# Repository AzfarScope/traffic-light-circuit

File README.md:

# traffic-light-circuit
This is a traffic light circuit using the decade counter ic CD4026BE and the timer ic NE555.

The circuit is made in Eagle Autodesk PCB design software.

Main point of this repository is for people to criticise and improve my schematic and circuit design to ensure proper results when I send it to a PCB manufacturing service such as JLCPCB or PCBWAY.

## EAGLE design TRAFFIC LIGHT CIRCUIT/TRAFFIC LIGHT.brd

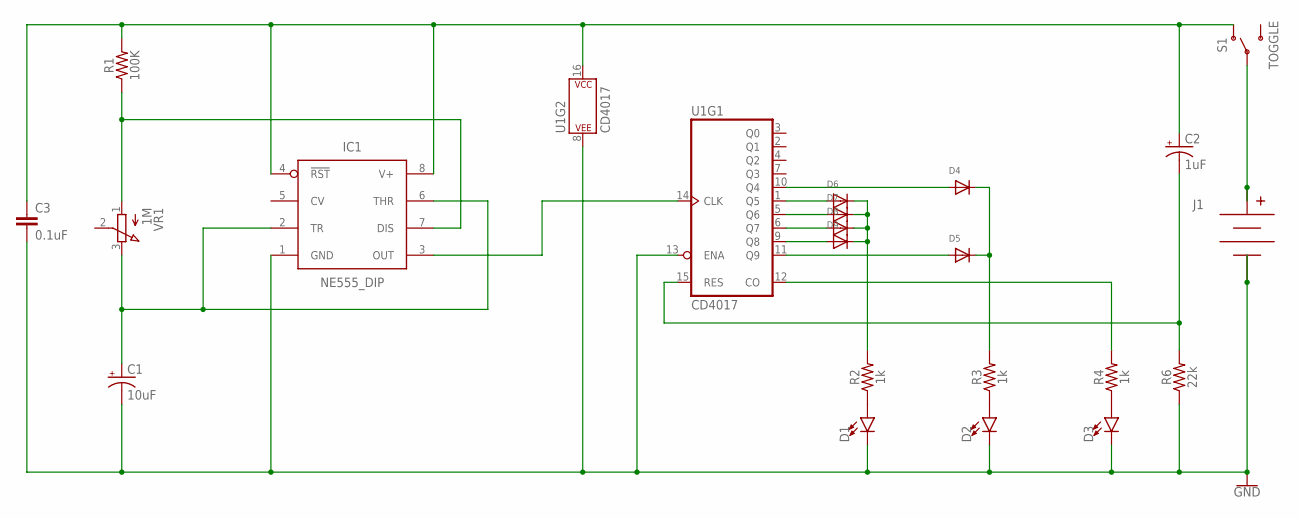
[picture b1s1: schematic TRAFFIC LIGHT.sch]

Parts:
C1: 10uF; E5-5
C2: 1uF; E5-5
C3: 0.1uF; CAP-PTH-SMALL-KIT
D1, D2, D3: LED5MM; LED_5MM
D4, D5, D6, D7, D8, D9: DIODEDO-1N4148; DO-1N4148
IC1: NE555_DIP; DIP826W53P254L959H508Q8B
J1: BC9VPC
R1: 100K; AXIAL-0.3
R2, R3, R4: 1k; AXIAL-0.3
R6: 22k; AXIAL-0.3
S1: TOGGLE; SWITCH-SPDT-PTH-8.5X3.7MM
U1: CD4017; DIP16
VR1: 1M; 3RP/1610N

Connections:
GND: C1.-, C3.2, D1.K (C), D2.K (C), D3.K (C), IC1.1 (GND), J1.V-, R6.P$1 (1), U1.8 (P$V-), U1.13 (ENA)
unnamed: D1.A, R2.P$1 (1)
unnamed: D2.A, R3.P$1 (1)
unnamed: D3.A, R4.P$1 (1)
unnamed: IC1.7 (DIS), R1.P$1 (1), VR1.1 (A)
unnamed: D4.A, U1.10 (Q4)
unnamed: IC1.3 (OUT), U1.14 (CLK)
unnamed: C1.+, IC1.2 (TR), IC1.6 (THR), VR1.3 (E)
unnamed: D5.A, U1.11 (Q9)
unnamed: D4.C, D5.C, R3.P$2 (2)
unnamed: D6.A, U1.1 (Q5)
unnamed: D7.A, U1.5 (Q6)
unnamed: C2.+, C3.1, IC1.4 (!RST), IC1.8 (V+), R1.P$2 (2), S1.1 (O), U1.16 (P$V+)
unnamed: R4.P$2 (2), U1.12 (CO)
unnamed: D8.A, U1.6 (Q7)
unnamed: D9.A, U1.9 (Q8)
unnamed: D6.C, D7.C, D8.C, D9.C, R2.P$2 (2)
unnamed: C2.-, R6.P$2 (2), U1.15 (RES)
unnamed: J1.V+, S1.2

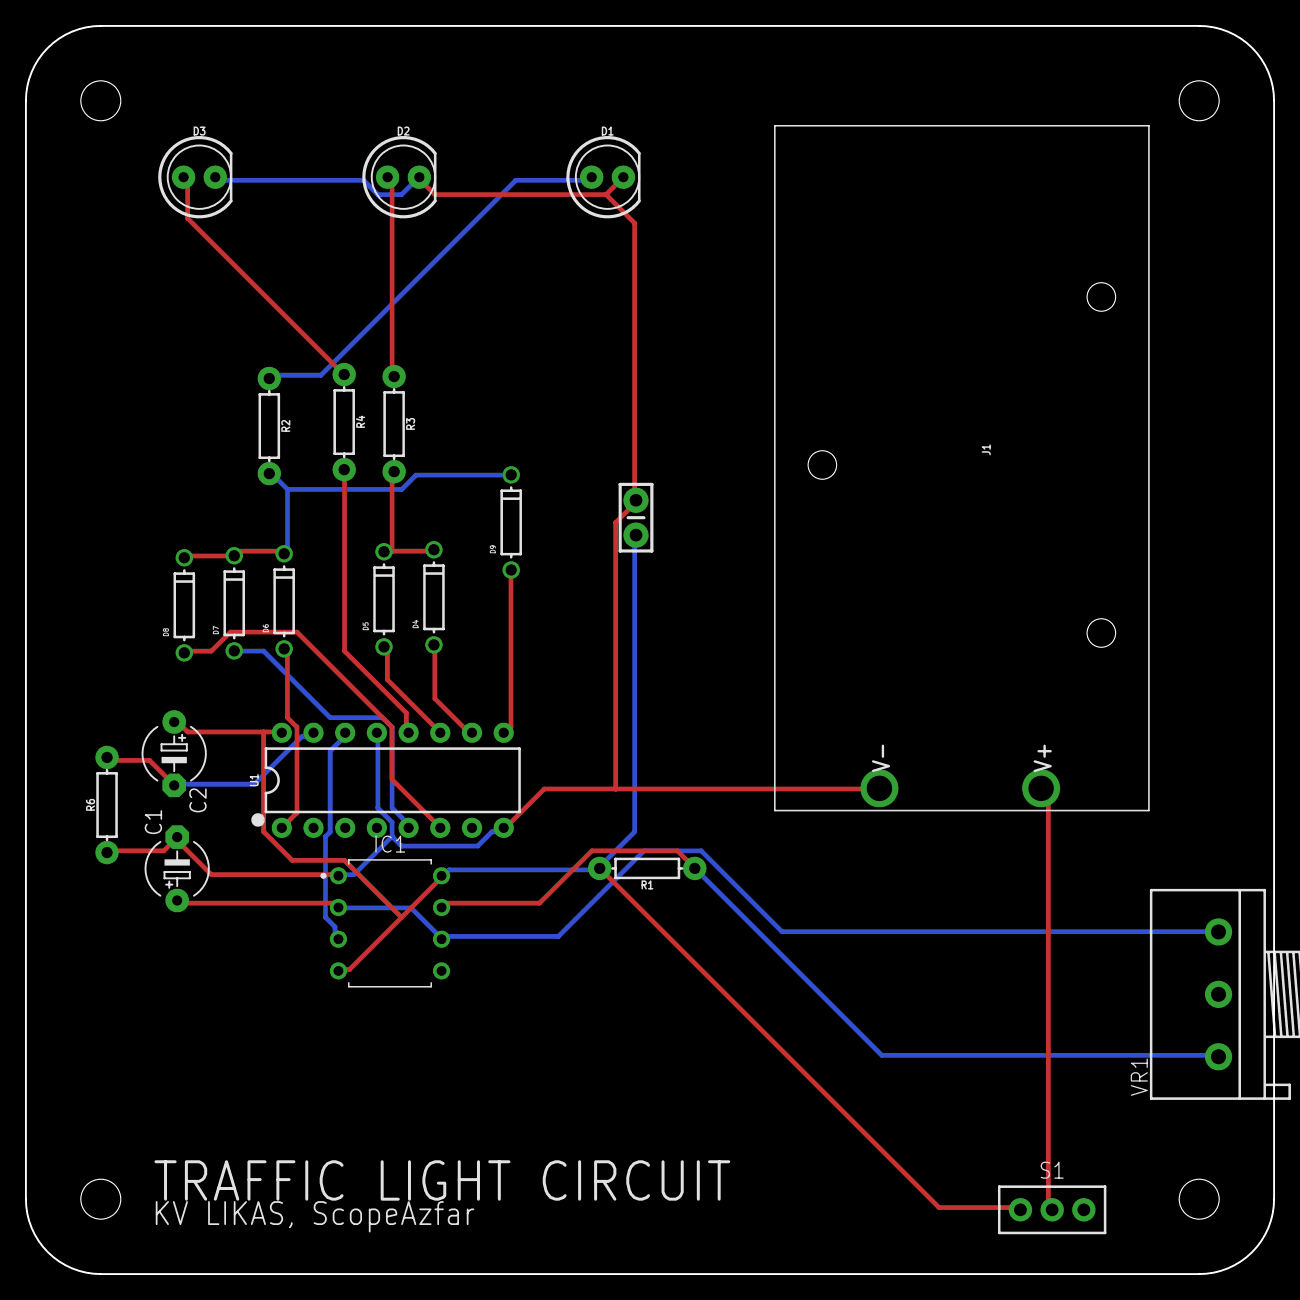
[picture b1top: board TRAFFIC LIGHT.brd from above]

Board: 2 copper layers, 100.0 x 100.0 mm, 22 parts (0 on the bottom side), 19 nets.

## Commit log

2023-08-01 README.md

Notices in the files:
parts and their libraries:
SparkFun-Capacitors: Licensing: Creative Commons ShareAlike 4.0 International - https://creativecommons.org/licenses/by-sa/4.0
